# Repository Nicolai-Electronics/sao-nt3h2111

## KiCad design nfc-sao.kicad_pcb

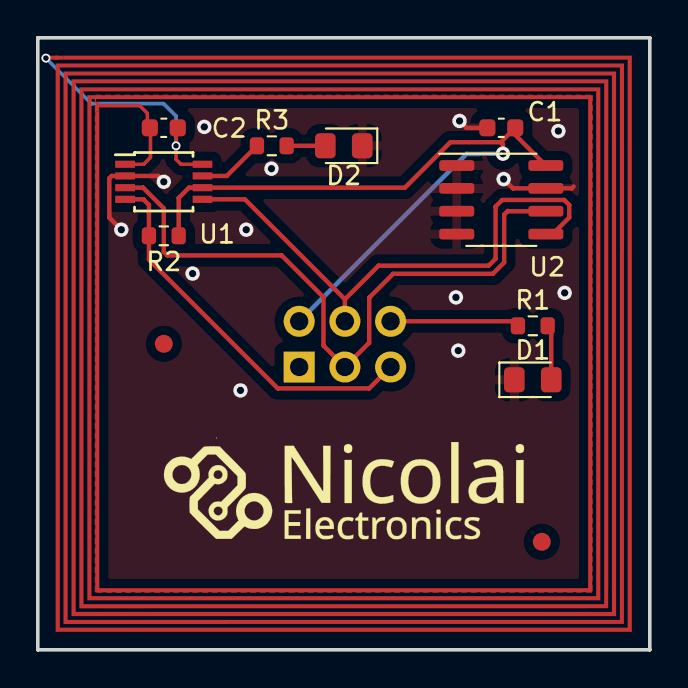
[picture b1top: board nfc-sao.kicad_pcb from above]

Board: 2 copper layers, 34.0 x 34.0 mm, 14 parts (0 on the bottom side), 11 nets.

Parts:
AE1: NFC antenna
C1: 100n; C_0603_1608Metric
C2: C_0603_1608Metric
D1, D2: LED; LED_0805_2012Metric_Pad1.15x1.40mm_HandSolder
FID1, FID2: Fiducial; Fiducial_1mm_Mask2mm
N1: Housing; nicolai
R1, R3: 200; R_0603_1608Metric
R2: 2k; R_0603_1608Metric
U1: TSSOP-8_3x3mm_P0.65mm
U2: EEPROM; SOIC-8_3.9x4.9mm_P1.27mm
X1: SAO; Badgelife-SAOv169-SAO-2x3

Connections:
+3.3V: C1.1, R2.1, U1.6 (VCC), U2.8 (VCC), X1.1 (VCC)
/INT: R2.2, U1.4 (FD), X1.6 (GPIO2)
/SCL: U1.3 (SCL), U2.6 (SCL), X1.4 (SCL)
/SDA: U1.5 (SDA), U2.5 (SDA), X1.3 (SDA)
GND: C1.2, D1.1 (K), D2.1 (K), U1.2 (VSS), U2.1 (A0), U2.2 (A1), U2.3 (A2), U2.4 (GND), U2.7 (WP), X1.2 (GND)
unnamed: D1.2 (A), R1.2
unnamed: D2.2 (A), R3.2
unnamed: AE1.2, C2.1, U1.1 (LA)
unnamed: AE1.1, C2.2, U1.8 (LB)
unnamed: R3.1, U1.7 (VOUT)
unnamed: R1.1, X1.5 (GPIO1)
